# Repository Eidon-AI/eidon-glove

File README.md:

# eidon-glove

A robust 16-DOF hand/finger tracking wearable standard Bluetooth Human Interface Device (BLE HID) designed for humanoid teleoperation and collecting embodied AI training datasets.

## Features

- **16-DOF Finger Tracking**: Full hand tracking with 16 Hall effect sensors for precise joint angle measurement
- **Wireless Connectivity**: Standard BLE HID protocol (~100Hz wireless transmission)
- **Multi-Mode Support**: Generic HID and gamepad modes with custom firmware
- **9-DOF Orientation Tracking**: Optional BNO085 IMU integration (Accelerometer/Gyro/Magnetometer)
- **Custom Hardware**: Purpose-built PCB with analog multiplexer for efficient sensor management
- **ESP32-C3 MCU**: Built-in BLE, WiFi, and battery charging capabilities
- **All-Day Battery**: 3.7V 2000mAh lithium polymer battery with power management
- **Wearable Design**: Fully 3D printable exoskeleton optimized for comfort and accuracy
- **Power Management**: Integrated power switch and LED status indicators

## Hardware Architecture

### Core Components
- **Microcontroller**: Seeed XIAO ESP32-C3 (RISC-V 32-bit @ 160MHz)
- **Sensors**: 16x Hall effect sensors + magnets for joint tracking
- **IMU**: BNO085 9-DOF sensor (optional)
- **Multiplexer**: Analog multiplexer for sensor input management
- **Battery**: 3.7V 2000mAh Li-Po with ETA4054S2F charging chip

### BOM
- Seeed XIAO ESP32-C3 [[Amazon](https://amzn.to/43tHIOO)]
- Hall Effect Sensor [[Amazon](https://amzn.to/4mQyvrq)]
- BNO085 IMU Module [[Amazon](https://amzn.to/3ZKFbNI)]
- Adjustable Hand Strap [[Amazon](https://amzn.to/4mLNEds)]
- Finger Velcro Loops [[Amazon](https://amzn.to/4kuzVpS)]
- Wire Zip Ties [[Amazon](https://amzn.to/4mFPDQp)]
- M2 Screws [[Amazon](https://amzn.to/45LmPQm)]
- Lipo Battery [[Amazon](https://amzn.to/3ZLaW9m)]
- Power Switch [[Amazon](https://amzn.to/4kTvcxY)]
- Status LED [[Amazon](https://amzn.to/43XH38d)]
- JST Connectors + Wires [[AliExpress](https://www.aliexpress.us/item/3256807031812901.html)] *(only if using custom PCB)*
- Multiplexer Module [[Amazon](https://amzn.to/3HiPO4a)] *(only if **NOT** using custom PCB)*

### Pin Configuration (XIAO ESP32-C3)

| Function | GPIO | Pin Label | Notes |
|----------|------|-----------|-------|
| **Multiplexer Control** |
| S0 | 10 | D10 | Multiplexer select bit 0 |
| S1 | 9 | D9 | Multiplexer select bit 1 |
| S2 | 6 | D4 | Multiplexer select bit 2 |
| S3 | 7 | D5 | Multiplexer select bit 3 |
| **User Interface** |
| Boot Button | 9 | D9 | Built-in XIAO button |
| Mode Button | 10 | D10 | PCB-mounted button |
| Status LED | 5 | D3 | Power/status indicator |
| **BNO085 IMU (Optional)** |
| I2C SDA | 21 | D6/TX | IMU data line |
| I2C SCL | 20 | D7/RX | IMU clock line |

## BNO085 IMU Integration (Optional)

The BNO085 9-DOF IMU provides orientation tracking to complement finger position data. This is an optional component that can be added for enhanced hand tracking capabilities.

### BNO085 Wiring

**I2C Connection:**
- **SDA**: GPIO 21 (D6/TX) - I2C Data line
- **SCL**: GPIO 20 (D7/RX) - I2C Clock line  
- **VCC**: 3.3V power supply
- **GND**: Ground connection
- **I2C Address**: 0x4B (default)

**Optional Connections:**
- **RST**: Not currently implemented (software reset used instead)
- **INT**: Interrupt pin (not used in current implementation)

### Important Notes

⚠️ **Multiplexer Pin Conflicts**: The current codebase has these remaining pin assignment conflicts:

1. **Button Conflicts**: Boot button (GPIO 9) and Mode button (GPIO 10) conflict with multiplexer pins S1 and S0

### BNO085 Software Configuration

The IMU is configured for:
- **Sensor Fusion**: Game Rotation Vector mode
- **Update Rate**: 200Hz (5ms intervals)  
- **Auto-Detection**: System continues operation if IMU is not connected
- **Data Output**: Quaternion format for orientation representation

Breakout Board Recommendation:

- GY-BNO085 Module [[Amazon](https://www.amazon.com/Teyleten-Robot-BNO085-Accuracy-Nine-Axis/dp/B0CL26J81F)]

## Getting Started

### Prerequisites
- PlatformIO IDE extension
- 3D printer for mechanical components
- PCB manufacturing (or breadboard for prototyping)
- Components listed in BOM (see PCB directory)

### Build Instructions
1. Clone this repository
2. Open firmware project in PlatformIO
3. Install dependencies (automatically handled by platformio.ini)
4. Build and upload to XIAO ESP32-C3
5. Assemble mechanical components
6. Calibrate sensors using built-in calibration mode

### Firmware Dependencies
- **ResponsiveAnalogRead** ^1.2.1: Sensor input filtering  
- **NimBLE-Arduino** ^1.4.1: Bluetooth Low Energy
- **Adafruit BNO08x** ^1.2.3: IMU sensor library

## Web Hand Visualizer

The eidon-glove includes a comprehensive web-based visualizer for real-time hand tracking data visualization and analysis.

### What It Is

A browser-based 3D hand visualization tool that:
- **Real-time 3D Hand Model**: Displays a detailed 3D hand that mirrors your glove movements
- **IMU Orientation Tracking**: Shows precise hand orientation using quaternion data from the BNO085 IMU
- **16-DOF Finger Tracking**: Visualizes all finger joint movements with color-coded angle displays
- **Multi-Device Support**: Can connect to multiple gloves and trackers simultaneously
- **Data Recording & Playback**: Record hand movements and play them back for analysis

### Key Features

- **🎯 Gimbal-Lock Free**: Stable orientation tracking without axis flipping at extreme angles
- **🔄 Auto-Reconnect**: Automatically reconnects to previously paired devices on page refresh  
- **🎨 Color-Coded Visualization**: Device-specific colors for easy identification
- **📊 Real-Time Data**: Live quaternion values, Euler angles, and joint positions
- **🎮 HID Protocol**: Uses standard Web HID API for direct browser connection
- **💾 Session Recording**: Capture and save hand movement sequences

### How to Use

1. **Open the Web App**: Navigate to `/web/index.html` in a modern browser (Chrome/Edge recommended)
2. **Connect Your Glove**: Click "Connect" and select your eidon-glove from the HID device list
3. **Calibrate**: Use the "Calibrate" button to zero the sensor baseline
4. **Visualize**: Watch the 3D hand model mirror your real hand movements in real-time

### Browser Requirements

- **Chrome 89+** or **Edge 89+** (Web HID API support required)
- **HTTPS Connection** (required for Web HID API)
- **Modern GPU** (WebGL support for 3D rendering)

### Technical Details

- **Communication**: Web HID API for direct glove communication
- **3D Rendering**: Three.js for WebGL-based hand visualization  
- **Coordinate System**: Optimized quaternion mapping `(x, z, -y, w)` for stable orientation
- **Update Rate**: ~60fps visualization with real-time sensor data
- **Data Format**: 24-byte HID reports containing joint angles + quaternion data

### Files

```
web/

```

The web visualizer provides an intuitive way to validate glove functionality, debug sensor issues, and demonstrate the full capabilities of the eidon-glove system.

## Project Structure

```
eidon-glove/
├── firmware/          # ESP32-C3 firmware (PlatformIO)
│   ├── src/           # Main source code
│   ├── lib/           # Custom libraries
│   └── platformio.ini # Build configuration
├── pcb/               # KiCad PCB design files
├── cad/               # 3D printable components
├── web/               # Web interface (if applicable)
│   ├── index.html         # Main web interface
│   ├── script.js          # Core visualization logic
│   ├── style.css          # UI styling
│   ├── tetris.html    # Simple Tetris game demo
│   └── piano.html     # Simple five key piano demo
└── images/            # Documentation images
```

## Inspired By

This project builds upon excellent open-source work:
- **[Project-Homunculus](https://github.com/nepyope/Project-Homunculus)**: Original 3D models and mechanical design
- **[finger-tracker](https://github.com/max-titov/finger-tracker)**: Original firmware architecture
- **[glove-v3](https://github.com/max-titov/glove-v3)**: Current PCB design foundation

## Contributing

Contributions are welcome! Please:
1. Fork the repository
2. Create a feature branch
3. Make your changes
4. Test thoroughly
5. Submit a pull request

## License

This project is released under an open-source license. See individual component repositories for specific licensing terms.

---

**Status**: Active development - hardware tested, firmware functional, documentation in progress.

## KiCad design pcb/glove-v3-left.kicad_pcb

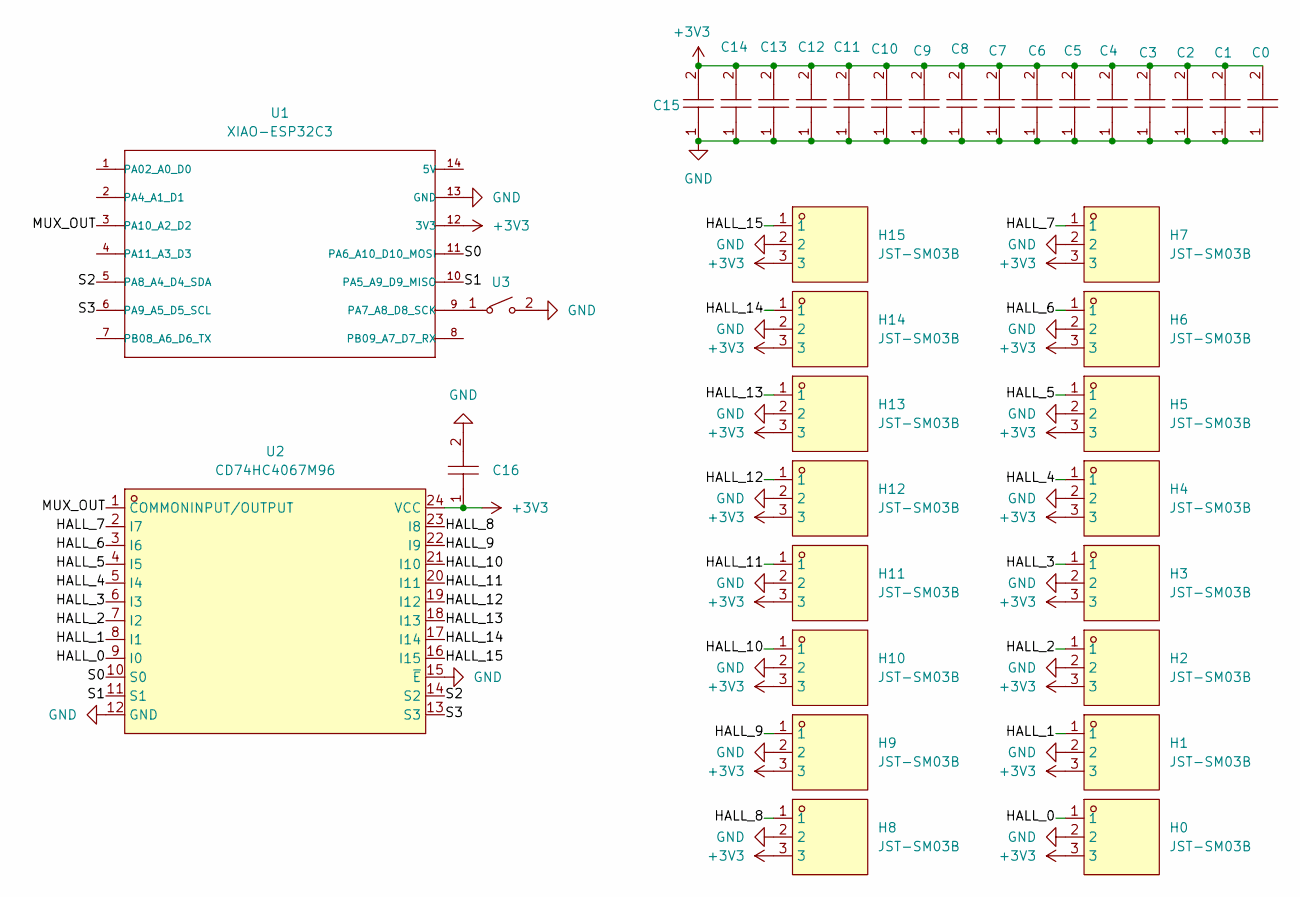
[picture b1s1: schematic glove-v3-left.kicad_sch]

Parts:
C0, C1, C2, C3, C4, C5, C6, C7, C8, C9, C10, C11, C12, C13, C14, C15, C16: C-0402-0.1uF-16V; C0402; LCSC Part C1525
H0, H1, H2, H3, H4, H5, H6, H7, H8, H9, H10, H11, H12, H13, H14, H15: JST-SM03B; CONN-SMD_SM03B-SRSS-TB-LF-SN-P; LCSC Part C160403
U1: XIAO-ESP32C3; MOUDLE14P-SMD-2.54-21X17.8MM
U2: CD74HC4067M96; SOIC-24_L15.4-W7.5-P1.27-LS10.3-BL; LCSC Part C496123
U3: 2.5x3mm-BUTTON; KEY-SMD_L3.0-W2.5-LS4.0_TD-1183SN; LCSC Part C2905193

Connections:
+3V3: C0.2, C1.2, C2.2, C3.2, C4.2, C5.2, C6.2, C7.2, C8.2, C9.2, C10.2, C11.2, C12.2, C13.2, C14.2, C15.2, C16.1, H0.3, H1.3, H2.3, H3.3, H4.3, H5.3, H6.3, H7.3, H8.3, H9.3, H10.3, H11.3, H12.3, H13.3, H14.3, H15.3, U1.12 (3V3), U2.24 (VCC)
/HALL_0: H0.1, U2.9 (I0)
/HALL_1: H1.1, U2.8 (I1)
/HALL_2: H2.1, U2.7 (I2)
/HALL_3: H3.1, U2.6 (I3)
/HALL_4: H4.1, U2.5 (I4)
/HALL_5: H5.1, U2.4 (I5)
/HALL_6: H6.1, U2.3 (I6)
/HALL_7: H7.1, U2.2 (I7)
/HALL_8: H8.1, U2.23 (I8)
/HALL_9: H9.1, U2.22 (I9)
/HALL_10: H10.1, U2.21 (I10)
/HALL_11: H11.1, U2.20 (I11)
/HALL_12: H12.1, U2.19 (I12)
/HALL_13: H13.1, U2.18 (I13)
/HALL_14: H14.1, U2.17 (I14)
/HALL_15: H15.1, U2.16 (I15)
/MUX_OUT: U1.3 (PA10_A2_D2), U2.1 (COMMONINPUT/OUTPUT)
/S0: U1.11 (PA6_A10_D10_MOSI), U2.10 (S0)
/S1: U1.10 (PA5_A9_D9_MISO), U2.11 (S1)
/S2: U1.5 (PA8_A4_D4_SDA), U2.14 (S2)
/S3: U1.6 (PA9_A5_D5_SCL), U2.13 (S3)
GND: C0.1, C1.1, C2.1, C3.1, C4.1, C5.1, C6.1, C7.1, C8.1, C9.1, C10.1, C11.1, C12.1, C13.1, C14.1, C15.1, C16.2, H0.2, H1.2, H2.2, H3.2, H4.2, H5.2, H6.2, H7.2, H8.2, H9.2, H10.2, H11.2, H12.2, H13.2, H14.2, H15.2, U1.13 (GND), U2.12 (GND), U2.15 (~E), U3.2
unnamed: U1.9 (PA7_A8_D8_SCK), U3.1

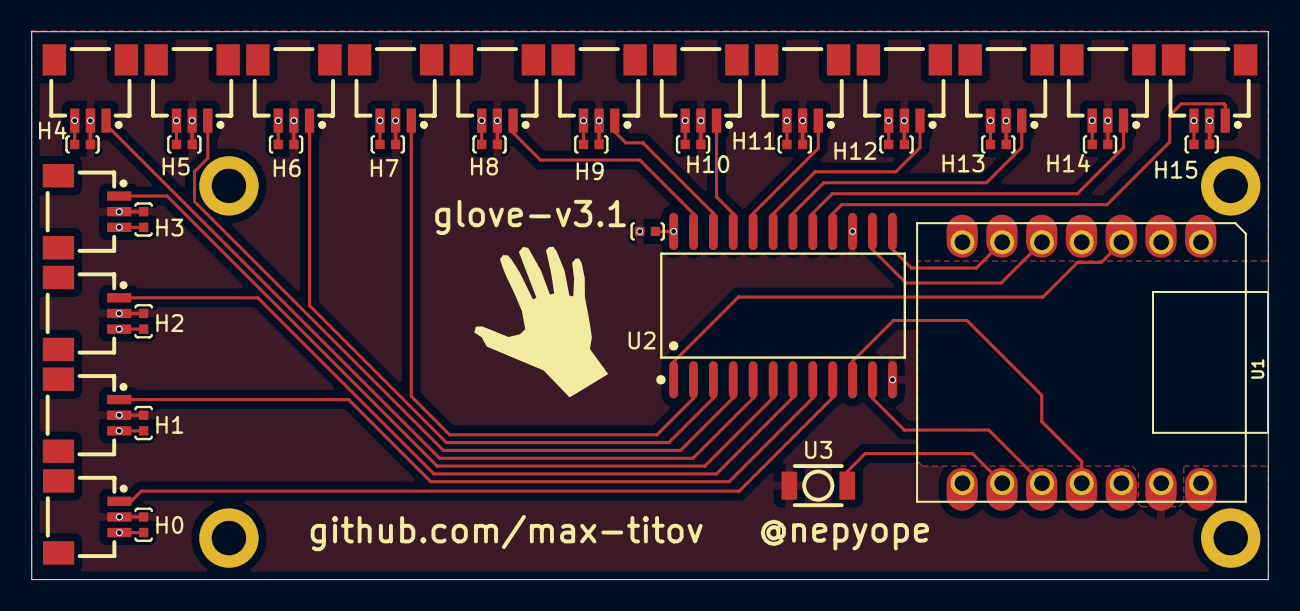
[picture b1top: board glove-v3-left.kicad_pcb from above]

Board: 4 copper layers, 79.0 x 35.0 mm, 36 parts (0 on the bottom side), 24 nets.

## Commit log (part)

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2025-03-18 updates latestest iteration of 3d printable parts and includes Fusion Archive and Bambu export files
2025-03-18 moar 3d model updates
2025-03-20 adds unique thumb 3d printed parts and updates base model files
2025-03-21 updates thumb and several slight changes to finger 3d model parts; updates firmware for custom PCB esp32 pins assigned to MUX
2025-03-27 refining angle calculations for glove v3
2025-03-27 fix web view for glove v3
2025-03-27 more tweaks to angle calc and adds tetris demo
2025-04-03 updates thumb models; adds gyro sensor support; updates web visualizer to use web hid
2025-04-07 adds further example code for IMU to attempt to calculate abs position but no luck :( also adds piano demo
2025-04-08 more IMU tweaking
2025-04-13 tweaks imu to gamepad analog movement; updates web visualizer to handle multiple gloves and arm trackers
2025-04-22 updates Fusion archive files to latest
2025-05-06 adds more eidon-tracker orientation visual vectors for web view
2025-05-06 updates quaternion values to pass over HID as 16-bit values; updates web visualizer for 16-bit quat; updates IMU to use game rotation vector
2025-05-07 calculating wrist flexion and deviation
2025-05-08 sorts devices with glove first
2025-05-09 orders trackers in a fixed order and starts experimenting with elbow; uses a pure quat to angle func for wrist
2025-05-09 swaps back to using projected line for measurements of wrist
2025-05-09 further elbow angle extraction, some shoulder action, and forearm/wrist rotation
2025-05-10 revamp web viz style; adds dark mode; works out bunch of kinks with device connection and disconnect; consolidates device-list into sidebar input values list
2025-05-12 fixes view control buttons; disables debugging logs; adds chained mode
2025-05-13 makes first tracker arrow vector shorter (for hand); implements calibration buttons to reset/tar IMU with a remote command
2025-05-14 fixes removal of tracker arrows upon device disconnection; improves base deviceId created from pid-vid-name; ui tweaks
2025-05-14 adds alternate palm model for left hand
2025-05-14 adds platformio shim in root so that platformio can detect project from root rather than opening a whole other vs code workspace with /firwmare folder as root
2025-05-14 adds missing shim pio file from last commit and implements unique advertised device name... ex: Eidon Glove-XXXX
2025-05-15 cleaning up some zombie code
2025-05-15 cleans up hid descriptor input report layout and corrects reportId
2025-05-15 implements HID output report to externally trigger IMU reset
2025-05-15 implements HID feature report for get/set device color
2025-05-15 adds .vscode settings to resolve ide intellisense errors for undefined libs
2025-05-16 prepends reportId to feature report response to stay consistent with how tracker ble stack behaves
2025-05-16 several web viz ui improvements
2025-05-16 updates web viz to detect device defined position; left/right, upper/lower
2025-05-16 cleans up style of device body posistion label tags
2025-05-16 restore first arrow length to be same as other tracker arrows rendered
2025-05-19 implements status led indicator in firmware and updates lid models for charge led hole and power toggle switch
2025-05-19 implements basic left vs right hand indicator in first bit of second buttons byte of data; moves boot button press to bit 1 of first buttons byte
2025-05-20 implements base device grouping and renders second arm tracker arrows
2025-05-20 maps glove buttons to hid buttons 1 and 2, then triggers calibration on trackers on the same arm when boot button is pressed
2025-05-27 flips quaternion forward direction since its mounted backwards within the glove; commits recent changes to web
2025-05-27 correctly flips IMU forward orientation
2025-05-28 fix: correctly oriented IMU quaternion so that yaw North is forward of the device based on datasheet
2025-05-31 Improve BNO085 robustness and prevent startup failures - Replace infinite loop with retry mechanism in BNO085 initialization - Add availability tracking and helper functions for graceful degradation 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
2025-05-31 Add persistent hall effect calibration with button reset - Store min/max angle calibration in flash memory to survive reboots - Auto-save calibration every 5 seconds when values change - Load saved c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
2025-06-04 updates readme, adds images, updated base Fusion archive file; removes unused dep from firmware; tweaks MCP final angles to offset difference between pinky/ring and index/middle fingers MCP placement
2025-06-04 Simplify web app to focus on glove sensor data with fixed IMU orientation
    Major simplifications and fixes:
    🎯 **Core Focus**: Streamlined app to focus purely on glove sensor data
    - Removed complex arm/body modeling in favor of hand-only display
    - Simplified UI to show essential glove data: IMU orientation + finger joints
    - Removed unnecessary coordinate transformation options that caused confusion
    🔄 **Fixed IMU Orientation Issues**:
2025-06-04 updates README with details about web hand visualizer tool
2025-06-04 updates readme and some fixes
2025-06-04 drops unused file to remove confusion around its use
2025-06-26 fix: resolves BNO085 communication
2025-06-26 fix: undefined HID_GENERIC var
2025-06-26 fix: corrects issue with hid report not sending
2025-06-28 fix: corrects issue with random disconnects and major improvement to ble data transmission speed
2025-07-02 feat: Add IMU reset functionality and fix HID output report compatibility
    - Add IMU reset via boot button (GPIO 9) with debouncing
    - Add HID output report support for remote IMU reset commands
    - Fix WebHID compatibility by separating input/output reports (Report ID 1/2)
    - Add feature report support for enhanced HID compatibility
    - Implement proper IMU reset sequence (disable/re-enable game rotation vector)
    - Add button interrupt handler and task for reliable button detection
2025-07-02 Refactor button logic into separate button.c/h module
    - Extract button functionality from main file into modular button.c/h
    - Add button initialization, callback system, and task management
    - Update CMakeLists.txt to include button.c in build
    - Fix conditional compilation issues with s_ble_hid_param usage
    - Improve code modularity and maintainability
2025-07-02 Major firmware refactoring and modularization
    - Refactor IMU code: rename adafruit_bno08x.c/h to imu.c/h for better organization
    - Add LED control module (led.c/h) for device status indication
    - Create descriptors directory with glove.h and tracker.h for HID report definitions
    - Remove obsolete files: README.md, sensor_descriptor.h, sdkconfig.old
    - Update Kconfig.projbuild for new component structure
    - Update esp_hid_gap.c with improved BLE handling
2025-07-03 Fix feature report to return only 3 RGB bytes without report ID
    - Add explicit Report ID 3 directive to HID descriptors for feature report
    - Update firmware to use Report ID 3 for feature report instead of Report ID 2
    - This should prevent the ESP-IDF HID stack from prepending report ID to data
    - Feature report now returns exactly 3 bytes: [R, G, B]
2025-07-03 Update web interface to always use last 3 bytes for RGB color
    - Replace offset-based logic with last 3 bytes approach
    - This handles both 3-byte and 4-byte responses robustly
    - Ensures RGB values are always extracted correctly regardless of report ID presence
2025-07-03 Create storage.c/h module for device-specific options and configurations
    - Rename preferences.c/h to storage.c/h to match hardware interface naming pattern
    - Move shell color storage functionality from main.c to storage module
    - Add support for body position storage (for future use)
    - Update all function names from preferences_* to storage_*
    - Clean up main.c by removing inline shell color functions
    - Update CMakeLists.txt to include storage.c
2025-07-03 Wire up button to send body position in HID reports
    - Use first 4 button bits (buttons 1-4) to encode body position value (0-3)
    - Button press cycles through positions 0, 1, 2, 3, then back to 0
    - Position value is included in every HID input report
    - Load position from storage on startup
    - Keep HID report size at 9 bytes (no extra position byte)
    - Button still triggers IMU reset in addition to position change
2025-07-03 Refactor to high-speed HID reporting with centralized state management
    - Add button_is_pressed() function to button.h/c for global button state access
    - Create high-speed HID reporting task (50Hz) that continuously sends reports
    - Move button and IMU logic to only update global state variables
    - Add change detection to avoid flooding with duplicate reports
    - Centralize all HID report sending in dedicated reporting task
    - Remove direct report sending from button callback and BNO085 task
2025-07-03 feat: improve HID output handling and LED strobe effects
    - Fix IMU reset via HID output reports: Handle empty output reports (len=0)
    as IMU reset triggers in addition to command 0x01
    - Implement smooth LED fade strobe effect: Replace abrupt on/off strobe with
    smooth sine wave fade using PWM for better visual experience
    - Add aggressive fade threshold: LED now goes completely off for ~70% of cycle
    with sharp rise to brightness for dramatic breathing effect
2025-07-09 feat: Increase IMU rate to 400Hz, HID to 100Hz, add auto-reconnect
    - Replace sh2 with bno08x_driver submodule for direct BNO085 control
    - Increase IMU update rate from 100Hz to 400Hz
    - Increase HID reporting rate from 50Hz to 100Hz
    - Add adaptive IMU polling to prevent CPU starvation
    - Fix IMU reset to maintain 400Hz configuration
    - Add auto-reconnect for HID devices in web interface
2025-07-09 chore: cleans up imu lib wrapper globals and sets default quaternion to valid forward direction
2025-07-09 refactor: break down main.c into feature-specific modules
    - Extract HID device functionality into dedicated hid_device module
    - Move HID report structures and state management
    - Move HID reporting task
    - Move feature report handling
    - Create clean API for HID operations (~260 lines moved)
    - Move IMU task from main.c to imu module
2025-07-09 refactor: extract device info module from main.c
    - Create dedicated device_info module for device identification
    - Move MAC-based device naming and serial number generation
    - Update serial number format to decimal + hex suffix
    - 10 decimal digits from last 4 MAC bytes
    - 4 hex digits from last 2 MAC bytes
    - Example: 01234567893456
2025-07-09 refactor: extract BLE HID module from main.c
    - Create dedicated BLE HID module for all Bluetooth LE HID functionality
    - Move BLE HID event callback handling (~250 lines)
    - Move task management functions (start_up/shut_down)
    - Move feature report handling and discovery
    - Move NimBLE-specific functions
    - Clean separation of BLE HID concerns from main application logic
2025-07-09 refactor: Further modularization and IMU stability improvements
    - Moved NVS flash initialization from main.c to storage.c
    - storage_init() now handles all NVS initialization
    - Better encapsulation of storage functionality
    - Moved Classic Bluetooth HID code to ble.c module
    - Even though Classic BT is now disabled
    - Keeps all Bluetooth-related code together
2025-07-10 feat: attempts to implement tare over hw reset but had mixed results
